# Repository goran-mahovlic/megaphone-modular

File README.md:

# megaphone-r5-modular
Modularised MEGAphone Design

This project is being carried out with the support of the NLnet Foundation under: https://nlnet.nl/project/MEGA65-MVP/

The goal of this project is to push the MEGAphone forward towards a Minimum Viable Product (MVP) in a cost-effective way by modularising the PCB
allowing for faster development and lower development costs as a result. Also, the modularisation helps to work around supply-chain problems by
allowing the replacement of hard to source components, without requiring a full PCB redesign.  Those modules can also be manufactured much more easily
in a domestic setting, as there is less cumulative chance of messing something up.  Alternatively, they can be manufactured in modest sized batches
using PCB fabrication places like PCBWay, who also offer an assembly option.

The following sections outline the tasks and their current state of progress, where appropriate.

## Task 1: Development and testing of core simple cellular telephony and text messaging software

The software aspect of this project relates to the software required to control and interact with the hardware modules, as well as to perform basic telephony functionality.

## Task 2: Modularisation and testing of the PCB design

The major hardware stream of this project is focused on modularising the MEGAphone PCB, so that the modules can be iterated and/or manufactured independently. This is to support both users self-manufacturing, so that the complexity of the fabrication process can be greatly simplified, as well as to allow for much faster and, including ad-hoc response to future supply chain challenges. 

### 2.1 High-efficiency DC-DC converter module to power the various sub-systems

High-current and high-efficiency modules are required for the main FPGA, cellular modem, auxilliary communications module, LCD panel, and external speaker/bluetooth modules.  It is desirable to come up with a single module that can be reused several times for these purposes.  The cellular modems are likely to be the highest draw item, and according to https://ww1.microchip.com/downloads/en/Appnotes/ANLPS300-APID.pdf, they can draw upto around 2A at 3.3V, which is the voltage we will most likely use, since it allows a common voltage for many of our sub-systems.

It is unlikely that any other device on the system will consume more power than this, so our DC-DC modules need to support 2A.

A further requirement is that it must be buck-boost, as the LiFePO4 cells can go below 3.3V, but when charged are >3.3V.

Some possible parts to consider:

STBBJ3 https://www.st.com/en/power-management/stbb3j.html  (2A in buck mode, i.e., where VIN > 3.3V, but only 800mA in boost mode, i.e., where VIN < 3.3V). 5x4 grid array, without thermal pad. Shutdown and soft-start. "typical" efficiency of 94%
LTC3113 https://www.analog.com/media/en/technical-documentation/data-sheets/3113f.pdf (3A in buck mode, 1.5A in boost mode). "up to" 96% efficiency. Choice of grid array and TSSOP -- but with a concealled thermal pad on the underside, which is not easy to hand-solder. AU$20 each for TTSOP!

### 2.2 Low-energy power-management module to minimise energy consumption of device, especially in low-power modes

### 2.3 Battery management and energy harvesting module to allow USB-C, integrated solar panel and external 12/24V vehicle battery power sources, and efficient management of the integrated rechargeable battery

### 2.4 Cellular modem communications module, including SIM card module

### 2.5 Internal microphone and speaker module

### 2.6 External speaker and bluetooth headset interface module

### 2.7 Primary FPGA carrier module, leveraging off-the-shelf FPGA modules if at all possible

### 2.8 LCD panel interface module

### 2.9 Auxiliary communications module, e.g., LoRa, ultra-sonic, infra-red or mm wave

Low-cost LoRa devices based on the SX1262 look to be an option, using open-source software like this: https://github.com/beegee-tokyo/SX126x-Mesh-Network
The goal would be for the module to be able to autonomously participate in the mesh while the main process is off.  ESP32s can go into low power modes with <1mA consumption according to https://www.arrow.com/en/research-and-events/articles/esp32-power-consumption-can-be-reduced-with-sleep-modes, and the SX1262 uses only about 5mA to listen for packets, and perhaps 70mA when active, so this looks plausible. The SX1262 when transmitting can draw upto about 120mA according to https://semtech.my.salesforce.com/sfc/p/#E0000000JelG/a/2R000000Un7F/yT.fKdAr9ZAo3cJLc4F2cBdUsMftpT2vsOICP7NmvMo

Thus the total power consumption of an auxilliary communications module (assuming we include an ESP32 in it, rather than using the power management FPGA to run the mesh) will be about 5mA while idle (~17mW) and upto ~200mA (~660mW).

### 2.10 Main carrier board and assembly, into which the various modules connect

## Task 3: Integration, Integration testing and remediation of the modules

Once the modules have been tested independently, this activity is focussed on testing the behaviour of the modules when connected to one another, including any VHDL/FPGA programming required to achieve this.

### 3.1 Requirements specification and analysis

### 3.2 Hardware integration and testing, including FPGA programming

### 3.3 Software integration and testing

### 3.4 Engage with and respond to security and accessibility audits

### 3.5 Remediation and contingency – for addressing any issues with the software and/or hardware components identified during the integration, and implementing or documenting appropriate solutions and/or work-arounds as appropriate

## Task 4: Preparation of Prototype Units

This activity focuses on taking the integrated hardware and software modules, and building a small number of units that are alpha-quality prototypes.  The specific objective is that they be integrated into units that are suitable for developers to use to continue development of both hardware and software of the system.  These units may be somewhat larger than the final obtainable footprint, depending on the costs of designing and fabricating the housings/enclosures.  The limited budget prevents the engagement of industrial designers who would be required for the completion of design for manufacture. Instead, we anticipate that the enclosures will be relatively simple 3D printed designs.
The remediation budget line is to allow for adjustment to the case design, the fabricated case and/or any of the hardware modules, so that the prototypes can be assembled and be as functional as possible.

### 4.1 Case Design

### 4.2 Case Fabrication

### 4.3 Assembly

### 4.4 Remediation / Mitigation, e.g., of any fitment issues, whether by adjustment of the case, reworking of a module or other means.

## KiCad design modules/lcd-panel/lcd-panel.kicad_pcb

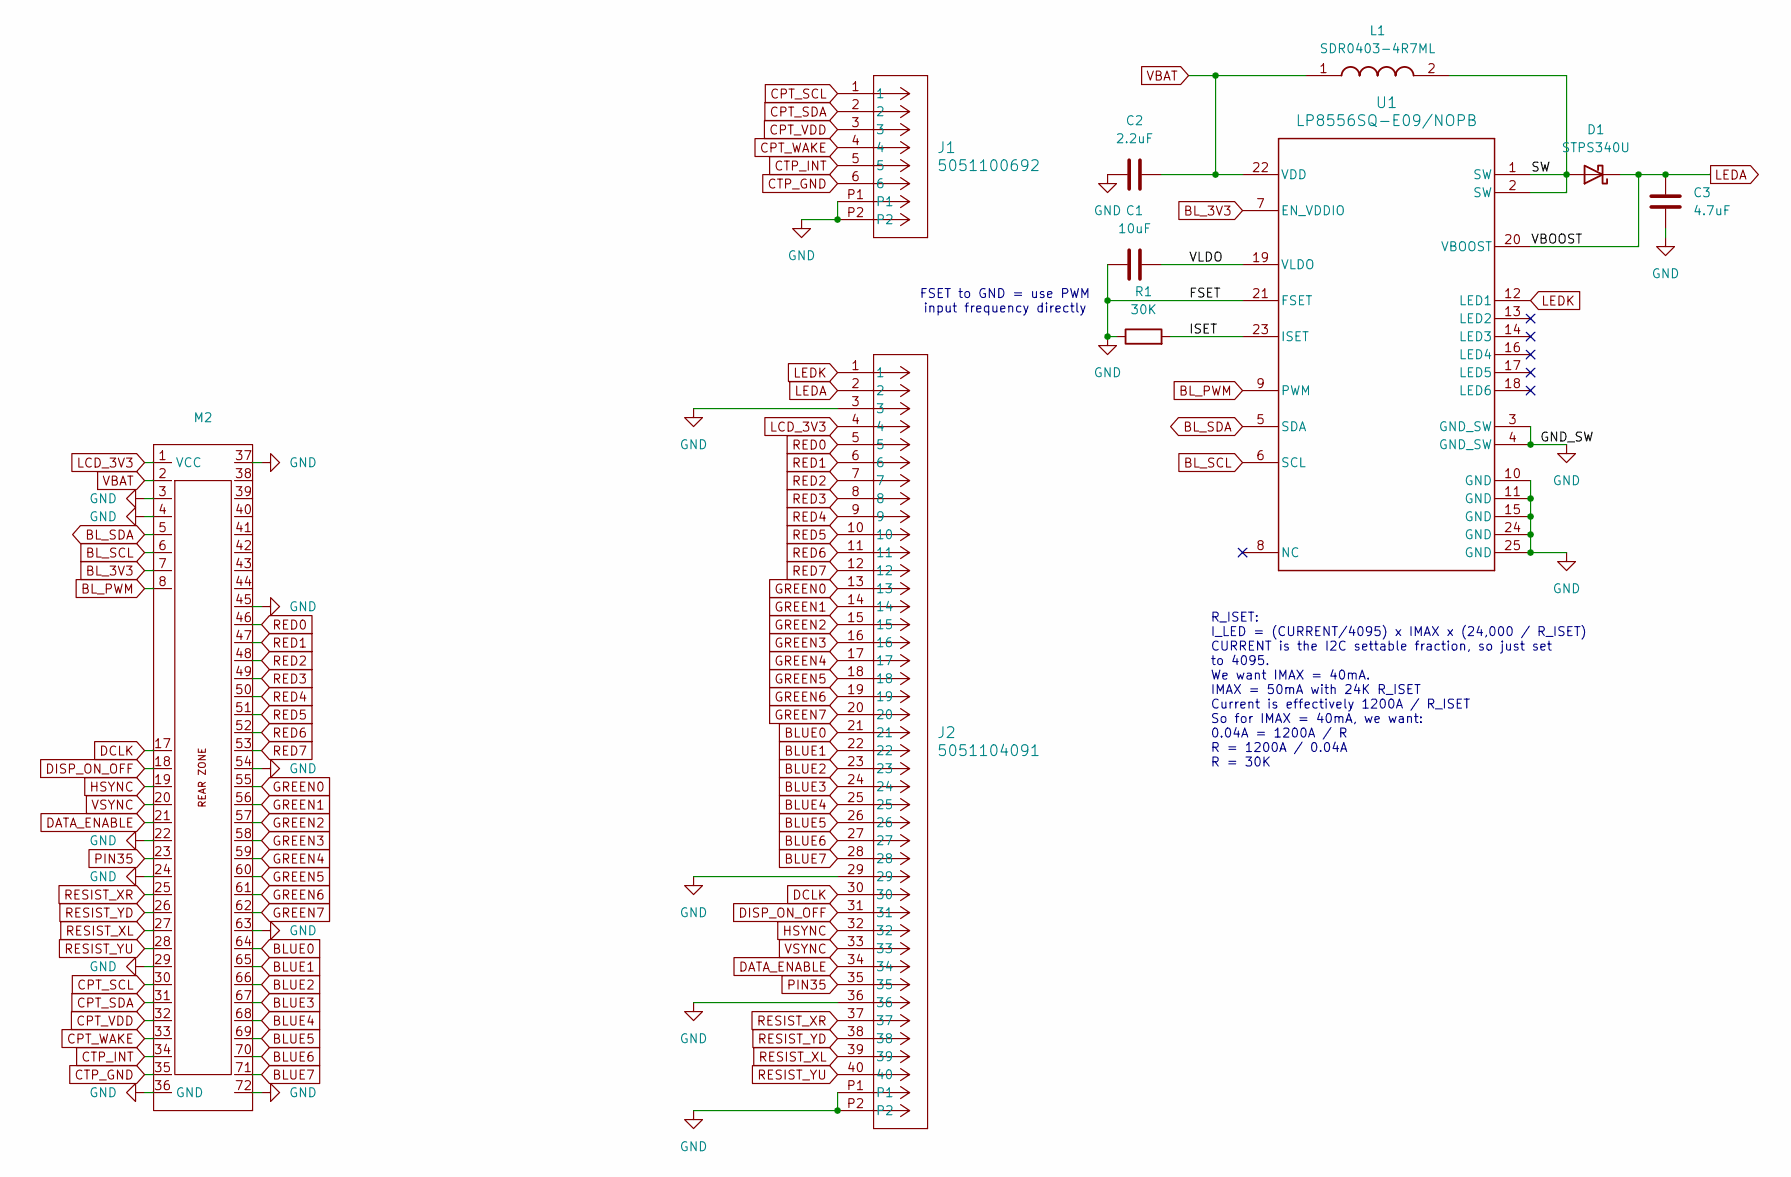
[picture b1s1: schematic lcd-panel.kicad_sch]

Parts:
C1: 10uF; C_0603_1608Metric_Pad1.08x0.95mm_HandSolder
C2: 2.2uF; C_0603_1608Metric_Pad1.08x0.95mm_HandSolder
C3: 4.7uF; C_0603_1608Metric_Pad1.08x0.95mm_HandSolder
D1: STPS340U; D_SOD-123
J1: 5051100692; CON_5051100692_MOL
J2: 5051104091; CON_5051104091_MOL
L1: SDR0403-4R7ML; SDR0403; Mouser Part Number 652-SDR0403-4R7ML
M2: MegaCastle2x36-Module-I40.0x86.6-MFFFFFFFFFFFFFF-SPAREPAD
R1: 30K; R_0603_1608Metric_Pad0.98x0.95mm_HandSolder
U1: LP8556SQ-E09/NOPB; RTW0024A

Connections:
/ISET: R1.2, U1.23 (ISET)
/SW: D1.2 (A), L1.2, U1.1 (SW), U1.2 (SW)
/VLDO: C1.2, U1.19 (VLDO)
BLUE0: J2.21, M2.64
BLUE1: J2.22, M2.65
BLUE2: J2.23, M2.66
BLUE3: J2.24, M2.67
BLUE4: J2.25, M2.68
BLUE5: J2.26, M2.69
BLUE6: J2.27, M2.70
BLUE7: J2.28, M2.71
BL_3V3: M2.7, U1.7 (EN_VDDIO)
BL_PWM: M2.8, U1.9 (PWM)
BL_SCL: M2.6, U1.6 (SCL)
BL_SDA: M2.5, U1.5 (SDA)
CPT_SCL: J1.1, M2.30
CPT_SDA: J1.2, M2.31
CPT_VDD: J1.3, M2.32
CPT_WAKE: J1.4, M2.33
CTP_GND: J1.6, M2.35
CTP_INT: J1.5, M2.34
DATA_ENABLE: J2.34, M2.21
DCLK: J2.30, M2.17
DISP_ON_OFF: J2.31, M2.18
GND: C1.1, C2.1, C3.2, J1.P1, J1.P2, J2.3, J2.29, J2.36, J2.P1, J2.P2, M2.3, M2.4, M2.22, M2.24, M2.29, M2.36 (GND), M2.37, M2.45, M2.54, M2.63, M2.72, R1.1, U1.3 (GND_SW), U1.4 (GND_SW), U1.10 (GND), U1.11 (GND), U1.15 (GND), U1.21 (FSET), U1.24 (GND), U1.25 (GND)
GREEN0: J2.13, M2.55
GREEN1: J2.14, M2.56
GREEN2: J2.15, M2.57
GREEN3: J2.16, M2.58
GREEN4: J2.17, M2.59
GREEN5: J2.18, M2.60
GREEN6: J2.19, M2.61
GREEN7: J2.20, M2.62
HSYNC: J2.32, M2.19
LCD_3V3: J2.4, M2.1 (VCC)
LEDA: C3.1, D1.1 (K), J2.2, U1.20 (VBOOST)
LEDK: J2.1, U1.12 (LED1)
PIN35: J2.35, M2.23
RED0: J2.5, M2.46
RED1: J2.6, M2.47
RED2: J2.7, M2.48
RED3: J2.8, M2.49
RED4: J2.9, M2.50
RED5: J2.10, M2.51
RED6: J2.11, M2.52
RED7: J2.12, M2.53
RESIST_XL: J2.39, M2.27
RESIST_XR: J2.37, M2.25
RESIST_YD: J2.38, M2.26
RESIST_YU: J2.40, M2.28
VBAT: C2.2, L1.1, M2.2, U1.22 (VDD)
VSYNC: J2.33, M2.20

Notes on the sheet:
FSET to GND = use PWM input frequency directly
R_ISET: I_LED = (CURRENT/4095) x IMAX x (24,000 / R_ISET) CURRENT is the I2C settable fraction, so just set to 4095. We want IMAX = 40mA. IMAX = 50mA with 24K R_ISET Current is effectively 1200A / R_ISET So for IMAX = 40mA, we want: 0.04A = 1200A / R R = 1200A / 0.04A R = 30K

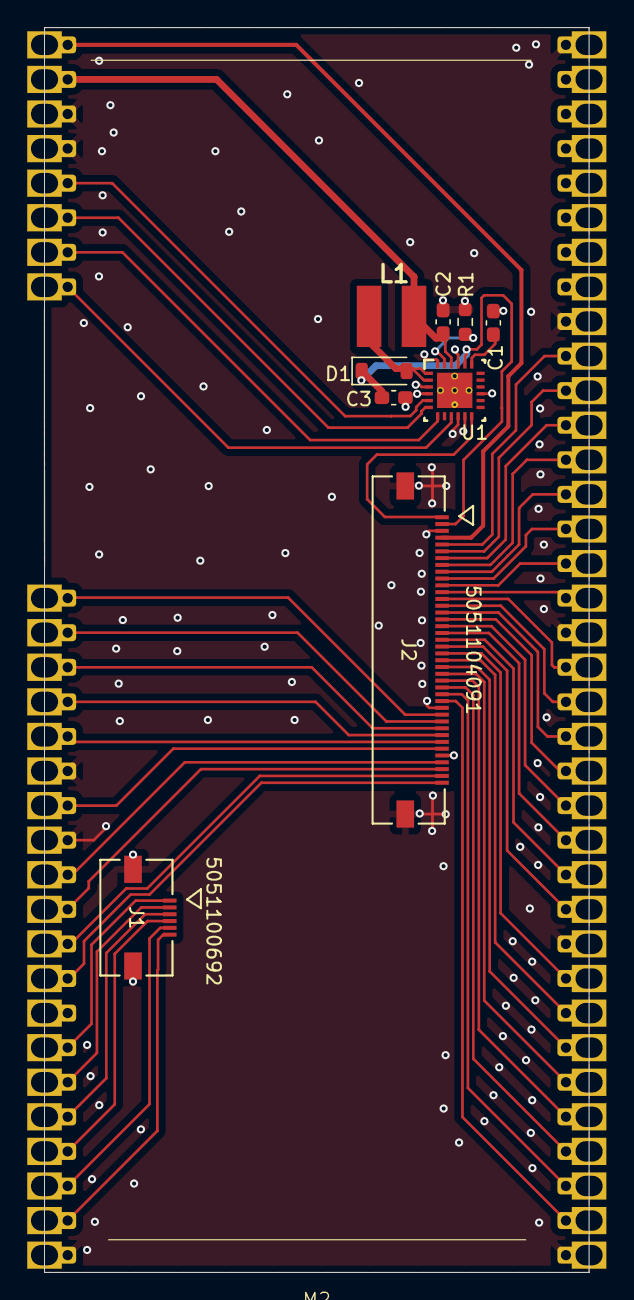
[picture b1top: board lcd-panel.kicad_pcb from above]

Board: 4 copper layers, 40.0 x 91.4 mm, 10 parts (0 on the bottom side), 52 nets.

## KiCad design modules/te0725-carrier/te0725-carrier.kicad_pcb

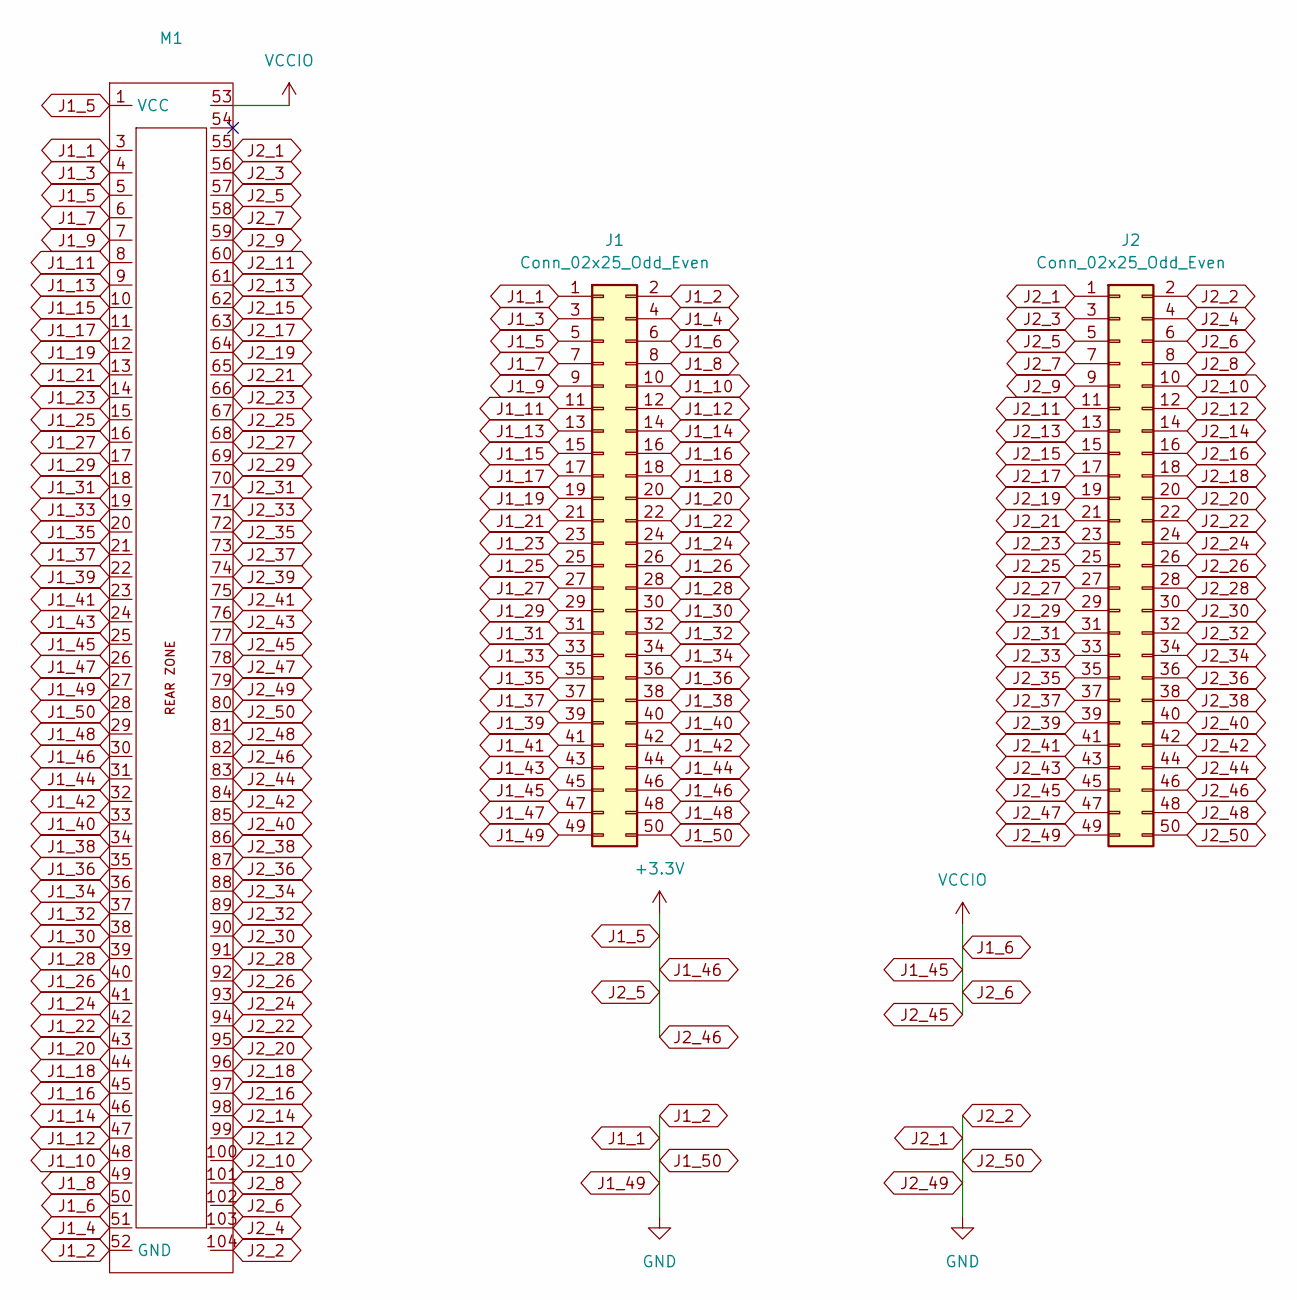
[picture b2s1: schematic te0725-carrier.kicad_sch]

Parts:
J1, J2: Conn_02x25_Odd_Even; PinHeader_2x25_P2.54mm_Vertical
M1: MegaCastle2x52-Module-I42.0x127.3-M1

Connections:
J1_1: J1.1, J1.2, J1.49, J1.50, J2.1, J2.2, J2.49, J2.50, M1.3, M1.27, M1.28, M1.52 (GND), M1.55, M1.79, M1.80, M1.104
J1_3: J1.3, M1.4
J1_4: J1.4, M1.51
J1_7: J1.7, M1.6
J1_8: J1.8, M1.49
J1_9: J1.9, M1.7
J1_10: J1.10, M1.48
J1_11: J1.11, M1.8
J1_12: J1.12, M1.47
J1_13: J1.13, M1.9
J1_14: J1.14, M1.46
J1_15: J1.15, M1.10
J1_16: J1.16, M1.45
J1_17: J1.17, M1.11
J1_18: J1.18, M1.44
J1_19: J1.19, M1.12
J1_20: J1.20, M1.43
J1_21: J1.21, M1.13
J1_22: J1.22, M1.42
J1_23: J1.23, M1.14
J1_24: J1.24, M1.41
J1_25: J1.25, M1.15
J1_26: J1.26, M1.40
J1_27: J1.27, M1.16
J1_28: J1.28, M1.39
J1_29: J1.29, M1.17
J1_30: J1.30, M1.38
J1_31: J1.31, M1.18
J1_32: J1.32, M1.37
J1_33: J1.33, M1.19
J1_34: J1.34, M1.36
J1_35: J1.35, M1.20
J1_36: J1.36, M1.35
J1_37: J1.37, M1.21
J1_38: J1.38, M1.34
J1_39: J1.39, M1.22
J1_40: J1.40, M1.33
J1_41: J1.41, M1.23
J1_42: J1.42, M1.32
J1_43: J1.43, M1.24
J1_44: J1.44, M1.31
J1_45: J1.6, J1.45, J2.6, J2.45, M1.25, M1.50, M1.53, M1.77, M1.102
J1_46: J1.5, J1.46, J2.5, J2.46, M1.1 (VCC), M1.5, M1.30, M1.57, M1.82
J1_47: J1.47, M1.26
J1_48: J1.48, M1.29
J2_3: J2.3, M1.56
J2_4: J2.4, M1.103
J2_7: J2.7, M1.58
J2_8: J2.8, M1.101
J2_9: J2.9, M1.59
J2_10: J2.10, M1.100
J2_11: J2.11, M1.60
J2_12: J2.12, M1.99
J2_13: J2.13, M1.61
J2_14: J2.14, M1.98
J2_15: J2.15, M1.62
J2_16: J2.16, M1.97
J2_17: J2.17, M1.63
J2_18: J2.18, M1.96
J2_19: J2.19, M1.64
J2_20: J2.20, M1.95
J2_21: J2.21, M1.65
J2_22: J2.22, M1.94
J2_23: J2.23, M1.66
J2_24: J2.24, M1.93
J2_25: J2.25, M1.67
J2_26: J2.26, M1.92
J2_27: J2.27, M1.68
J2_28: J2.28, M1.91
J2_29: J2.29, M1.69
J2_30: J2.30, M1.90
J2_31: J2.31, M1.70
J2_32: J2.32, M1.89
J2_33: J2.33, M1.71
J2_34: J2.34, M1.88
J2_35: J2.35, M1.72
J2_36: J2.36, M1.87
J2_37: J2.37, M1.73
J2_38: J2.38, M1.86
J2_39: J2.39, M1.74
J2_40: J2.40, M1.85
J2_41: J2.41, M1.75
J2_42: J2.42, M1.84
J2_43: J2.43, M1.76
J2_44: J2.44, M1.83
J2_47: J2.47, M1.78
J2_48: J2.48, M1.81

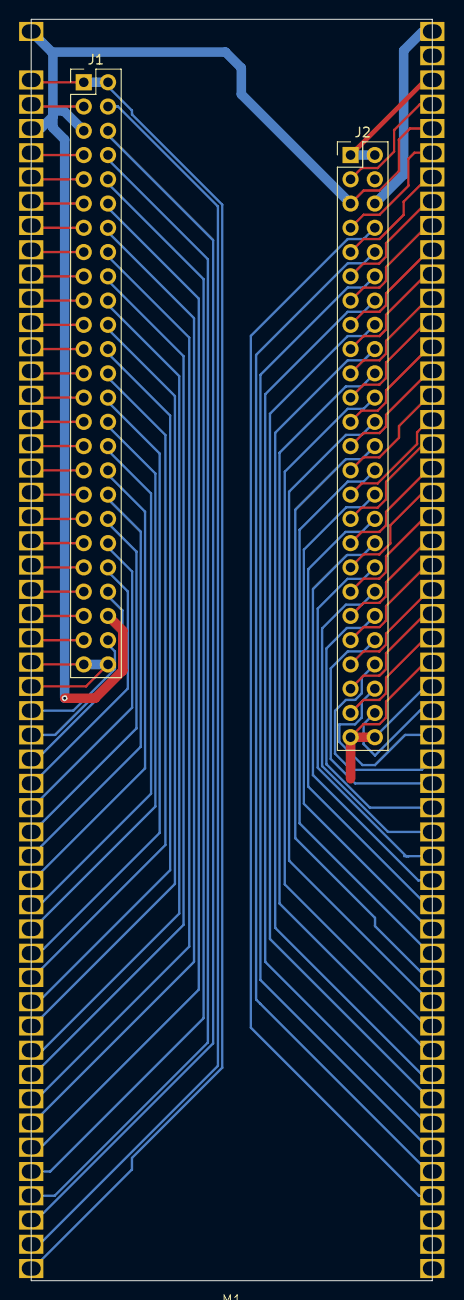
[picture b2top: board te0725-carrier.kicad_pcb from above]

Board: 2 copper layers, 42.0 x 132.1 mm, 3 parts (0 on the bottom side), 87 nets.

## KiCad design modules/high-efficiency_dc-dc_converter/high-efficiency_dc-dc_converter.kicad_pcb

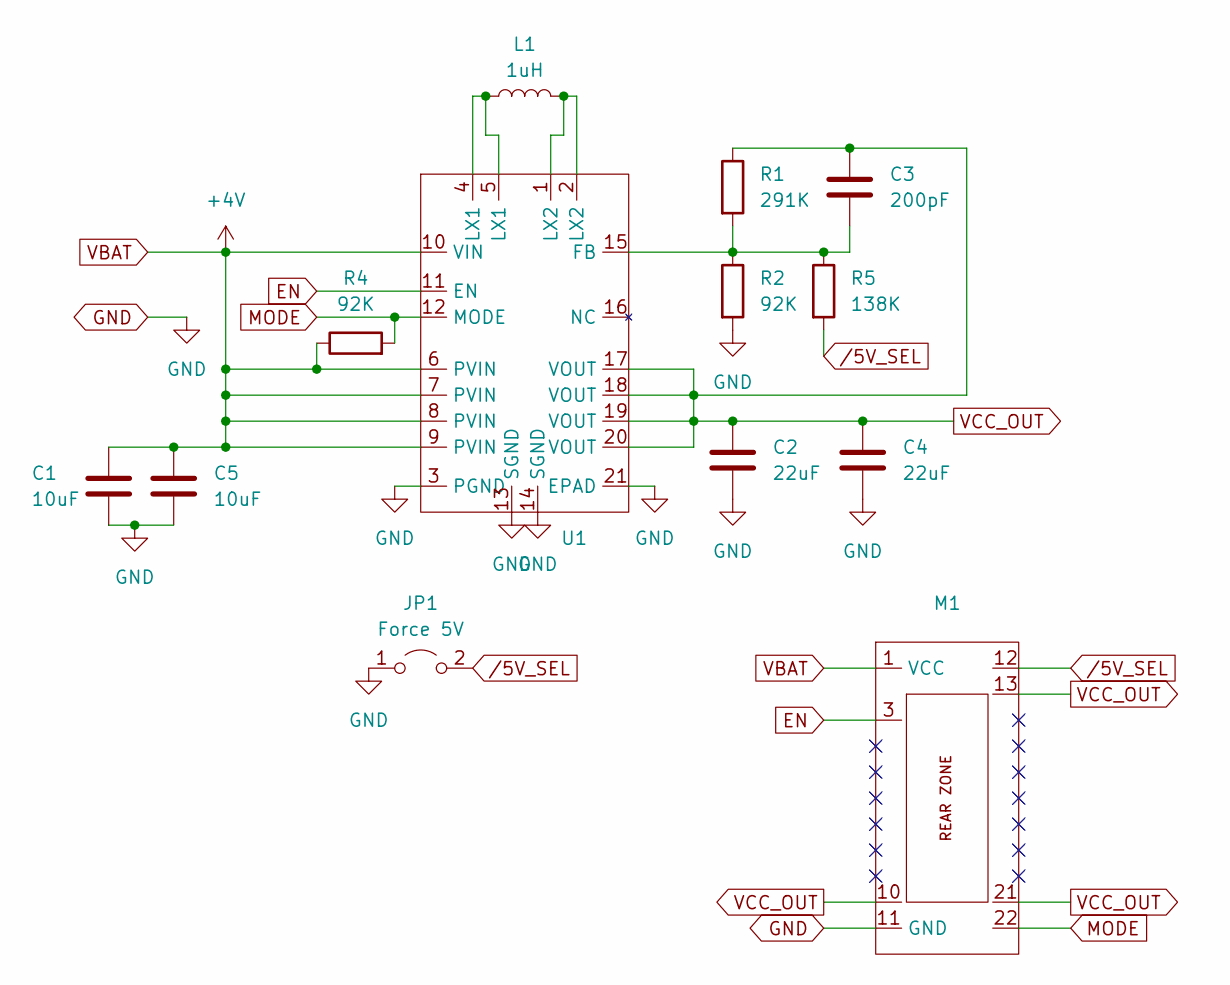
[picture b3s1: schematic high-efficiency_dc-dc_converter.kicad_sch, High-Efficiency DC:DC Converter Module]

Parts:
C1, C5: 10uF; C_0805_2012Metric
C2, C4: 22uF; C_0805_2012Metric
C3: 200pF; C_0805_2012Metric
JP1: Force 5V; SolderJumper-2_P1.3mm_Open_RoundedPad1.0x1.5mm
L1: 1uH; L_1008_2520Metric
M1: MegaCastle2x11-Module-I15.7x23.1-MA0780C-PANEL-NIBBLE
R1: 291K; R_0603_1608Metric
R2, R4: 92K; R_0603_1608Metric
R5: 138K; R_0603_1608Metric
U1: QFN50P400X400X90-21N

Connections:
EN: M1.3, U1.11 (EN)
GND: C1.2, C2.2, C4.2, C5.2, JP1.1 (A), M1.11 (GND), R2.2, U1.3 (PGND), U1.13 (SGND), U1.14 (SGND), U1.21 (EPAD)
MODE: M1.22, R4.2, U1.12 (MODE)
unnamed: L1.1, U1.4 (LX1), U1.5 (LX1)
unnamed: L1.2, U1.1 (LX2), U1.2 (LX2)
unnamed: C3.2, R1.2, R2.1, R5.1, U1.15 (FB)
VBAT: C1.1, C5.1, M1.1 (VCC), R4.1, U1.6 (PVIN), U1.7 (PVIN), U1.8 (PVIN), U1.9 (PVIN), U1.10 (VIN)
VCC_OUT: C2.1, C3.1, C4.1, M1.10, M1.13, M1.21, R1.1, U1.17 (VOUT), U1.18 (VOUT), U1.19 (VOUT), U1.20 (VOUT)
/5V_SEL: JP1.2 (B), M1.12, R5.2

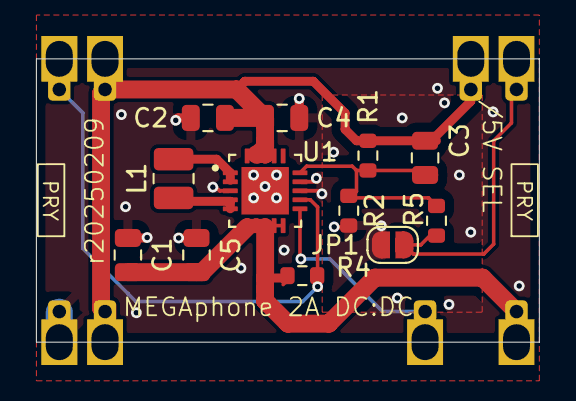
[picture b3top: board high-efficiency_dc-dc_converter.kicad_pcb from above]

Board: 2 copper layers, 27.9 x 15.7 mm, 13 parts (1 on the bottom side), 9 nets.

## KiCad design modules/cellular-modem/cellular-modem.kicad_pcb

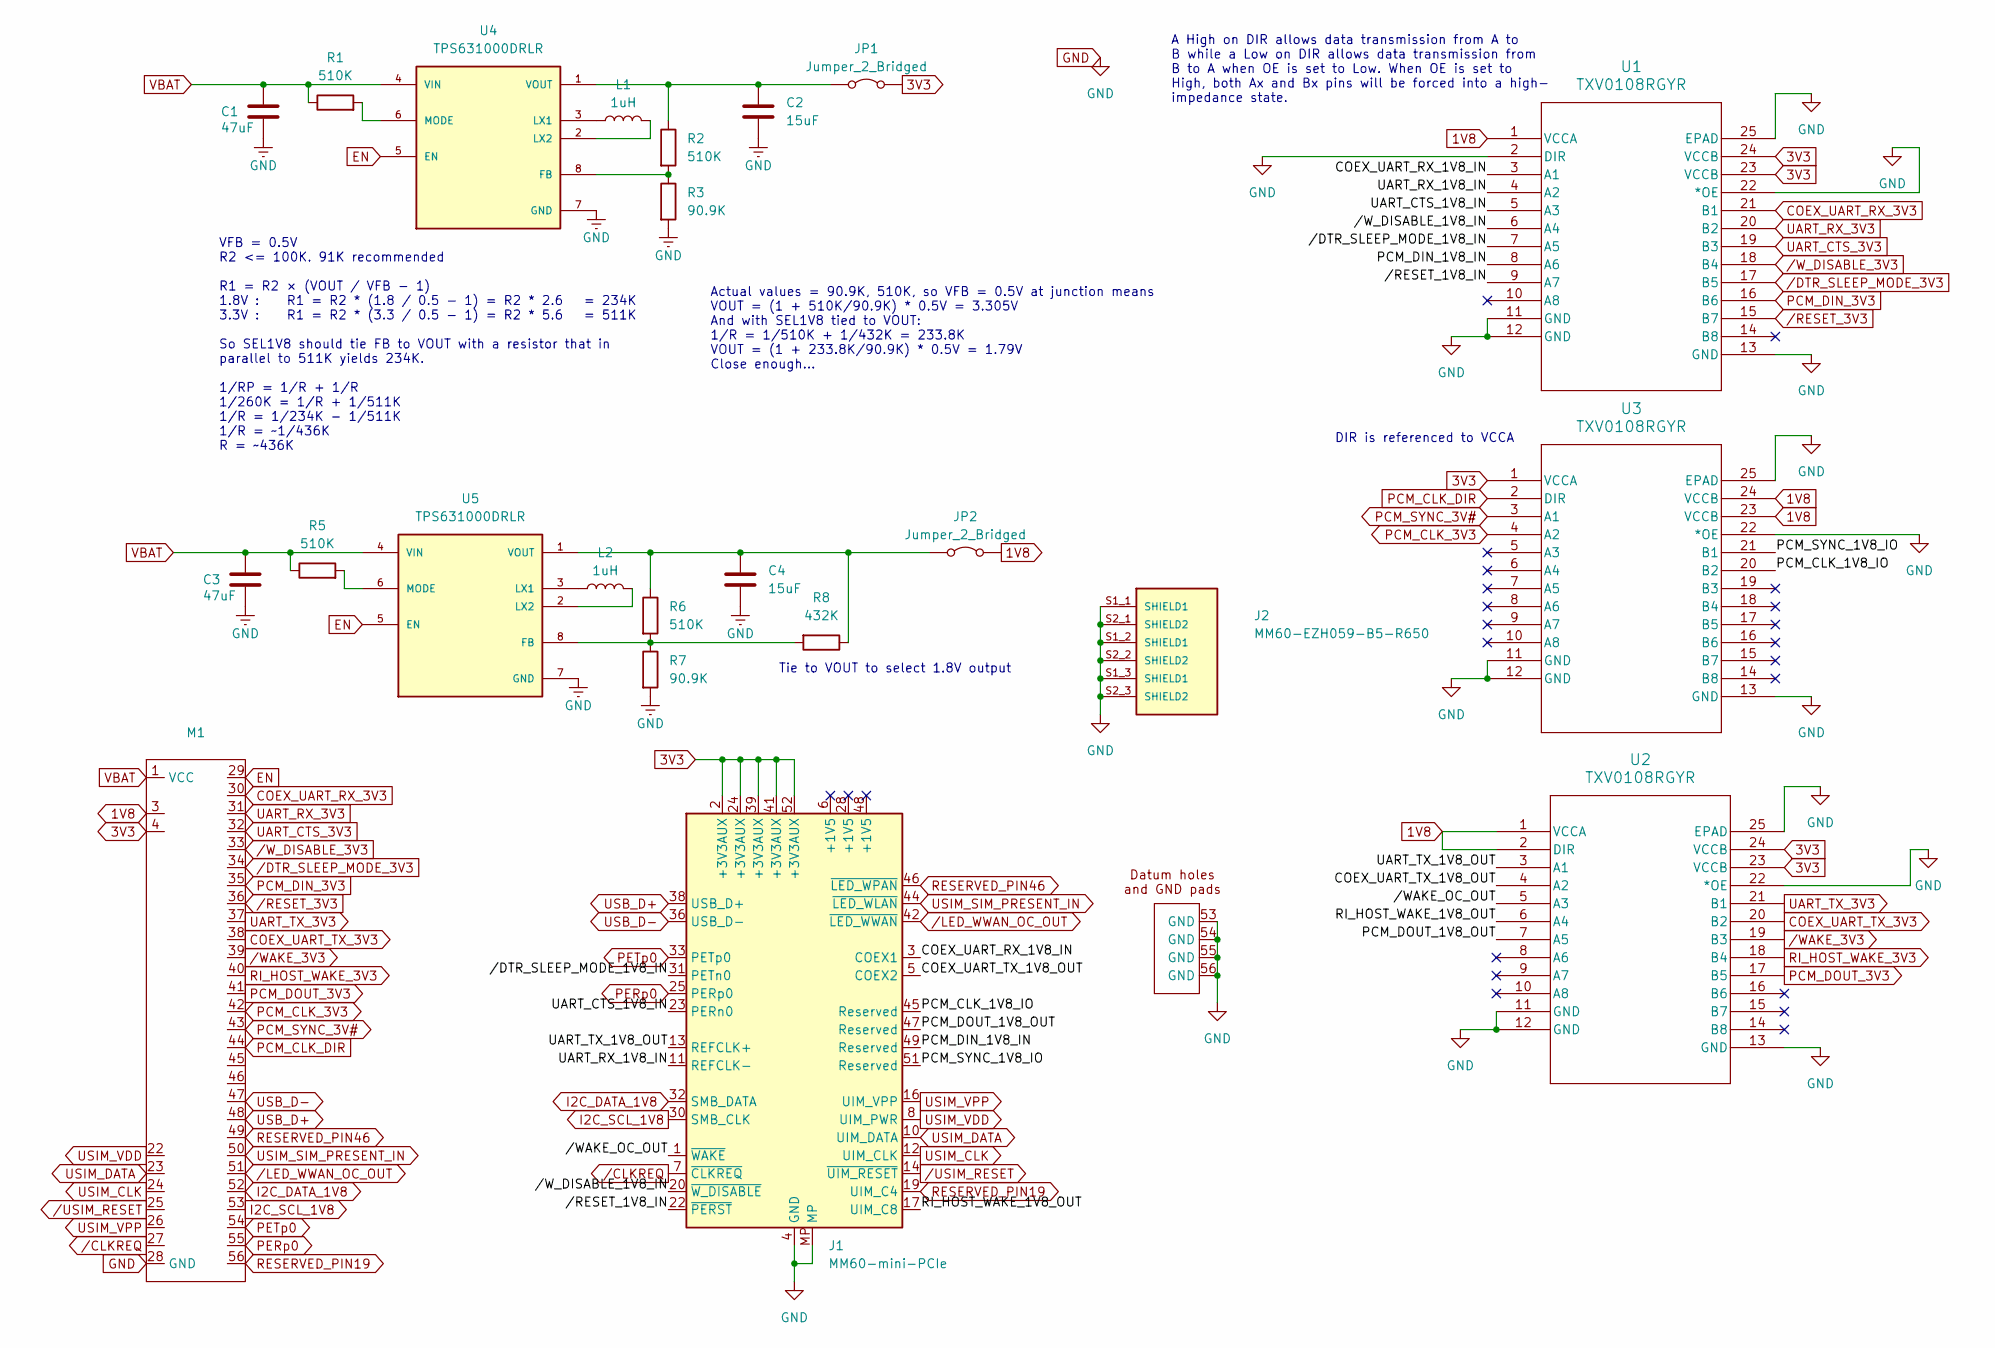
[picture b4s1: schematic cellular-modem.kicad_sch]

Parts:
C1, C3: 47uF; C_0805_2012Metric
C2, C4: 15uF; C_0805_2012Metric
J1: MM60-mini-PCIe; CONN_MM60-52B1-E1-R650_JAE
J2: MM60-EZH059-B5-R650; JAE_MM60-EZH059-B5-R650; PARTREV 3
JP1, JP2: Jumper_2_Bridged; SolderJumper-2_P1.3mm_Bridged2Bar_RoundedPad1.0x1.5mm
L1, L2: 1uH; L_1008_2520Metric_Pad1.43x2.20mm_HandSolder
M1: MegaCastle2x28-Module-I36.0x66.3-MB00007FFFFFFFF-NIBBLE
R1, R2, R5, R6: 510K; R_0805_2012Metric
R3, R7: 90.9K; R_0805_2012Metric
R8: 432K; R_0805_2012Metric
U1, U2, U3: TXV0108RGYR; VQFN24_RGY_TEX
U4, U5: TPS631000DRLR; SOT50P160X60-8N; PARTREV B

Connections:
1V8: JP2.2 (B), M1.3, U1.1 (VCCA), U2.1 (VCCA), U2.2 (DIR), U3.23 (VCCB), U3.24 (VCCB)
3V3: J1.2 (+3V3AUX), J1.24 (+3V3AUX), J1.39 (+3V3AUX), J1.41 (+3V3AUX), J1.52 (+3V3AUX), JP1.2 (B), M1.4, U1.23 (VCCB), U1.24 (VCCB), U2.23 (VCCB), U2.24 (VCCB), U3.1 (VCCA)
/COEX_UART_RX_1V8_IN: J1.3 (COEX1), U1.3 (A1)
/COEX_UART_TX_1V8_OUT: J1.5 (COEX2), U2.4 (A2)
/PCM_CLK_1V8_IO: J1.45 (Reserved), U3.20 (B2)
/PCM_DIN_1V8_IN: J1.49 (Reserved), U1.8 (A6)
/PCM_DOUT_1V8_OUT: J1.47 (Reserved), U2.7 (A5)
/PCM_SYNC_1V8_IO: J1.51 (Reserved), U3.21 (B1)
/RI_HOST_WAKE_1V8_OUT: J1.17 (UIM_C8), U2.6 (A4)
/UART_CTS_1V8_IN: J1.23 (PERn0), U1.5 (A3)
/UART_RX_1V8_IN: J1.11 (REFCLK-), U1.4 (A2)
/UART_TX_1V8_OUT: J1.13 (REFCLK+), U2.3 (A1)
//DTR_SLEEP_MODE_1V8_IN: J1.31 (PETn0), U1.7 (A5)
//RESET_1V8_IN: J1.22 (~PERST), U1.9 (A7)
//WAKE_OC_OUT: J1.1 (~WAKE), U2.5 (A3)
//W_DISABLE_1V8_IN: J1.20 (~W_DISABLE), U1.6 (A4)
COEX_UART_RX_3V3: M1.30, U1.21 (B1)
COEX_UART_TX_3V3: M1.38, U2.20 (B2)
EN: M1.29, U4.5 (EN), U5.5 (EN)
GND: C1.1, C2.2, C3.1, C4.2, J1.4 (GND), J1.9 (GND), J1.15 (GND), J1.18 (GND), J1.21 (GND), J1.26 (GND), J1.27 (GND), J1.29 (GND), J1.34 (GND), J1.35 (GND), J1.37 (GND), J1.40 (GND), J1.43 (GND), J1.50 (GND), J1.53 (GND), J1.54 (GND), J1.55 (GND), J1.56 (GND), J1.MP, J2.S1_1 (SHIELD1), J2.S1_2 (SHIELD1), J2.S1_3 (SHIELD1), J2.S2_1 (SHIELD2), J2.S2_2 (SHIELD2), J2.S2_3 (SHIELD2), M1.28 (GND), R3.2, R7.2, U1.2 (DIR), U1.11 (GND), U1.12 (GND), U1.13 (GND), U1.22 (*OE), U1.25 (EPAD), U2.11 (GND), U2.12 (GND), U2.13 (GND), U2.22 (*OE), U2.25 (EPAD), U3.11 (GND), U3.12 (GND), U3.13 (GND), U3.22 (*OE), U3.25 (EPAD), U4.7 (GND), U5.7 (GND)
I2C_DATA_1V8: J1.32 (SMB_DATA), M1.52
I2C_SCL_1V8: J1.30 (SMB_CLK), M1.53
unnamed: C2.1, JP1.1 (A), R2.1, U4.1 (VOUT)
unnamed: C4.1, JP2.1 (A), R6.1, R8.1, U5.1 (VOUT)
unnamed: R2.2, R3.1, U4.8 (FB)
unnamed: L1.1, U4.3 (LX1)
unnamed: L1.2, U4.2 (LX2)
unnamed: R1.2, U4.6 (MODE)
unnamed: R6.2, R7.1, R8.2, U5.8 (FB)
unnamed: L2.1, U5.3 (LX1)
unnamed: L2.2, U5.2 (LX2)
unnamed: R5.2, U5.6 (MODE)
PCM_CLK_3V3: M1.42, U3.4 (A2)
PCM_CLK_DIR: M1.44, U3.2 (DIR)
PCM_DIN_3V3: M1.35, U1.16 (B6)
PCM_DOUT_3V3: M1.41, U2.17 (B5)
PCM_SYNC_3V#: M1.43, U3.3 (A1)
PERp0: J1.25 (PERp0), M1.55
PETp0: J1.33 (PETp0), M1.54
RESERVED_PIN19: J1.19 (UIM_C4), M1.56
RESERVED_PIN46: J1.46 (~LED_WPAN), M1.49
RI_HOST_WAKE_3V3: M1.40, U2.18 (B4)
UART_CTS_3V3: M1.32, U1.19 (B3)
UART_RX_3V3: M1.31, U1.20 (B2)
UART_TX_3V3: M1.37, U2.21 (B1)
USB_D+: J1.38 (USB_D+), M1.48
USB_D-: J1.36 (USB_D-), M1.47
USIM_CLK: J1.12 (UIM_CLK), M1.24
USIM_DATA: J1.10 (UIM_DATA), M1.23
USIM_SIM_PRESENT_IN: J1.44 (~LED_WLAN), M1.50
USIM_VDD: J1.8 (UIM_PWR), M1.22
USIM_VPP: J1.16 (UIM_VPP), M1.26
VBAT: C1.2, C3.2, M1.1 (VCC), R1.1, R5.1, U4.4 (VIN), U5.4 (VIN)
/CLKREQ: J1.7 (~CLKREQ), M1.27
/DTR_SLEEP_MODE_3V3: M1.34, U1.17 (B5)
/LED_WWAN_OC_OUT: J1.42 (~LED_WWAN), M1.51
/RESET_3V3: M1.36, U1.15 (B7)
/USIM_RESET: J1.14 (~UIM_RESET), M1.25
/WAKE_3V3: M1.39, U2.19 (B3)
/W_DISABLE_3V3: M1.33, U1.18 (B4)

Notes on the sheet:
Tie to VOUT to select 1.8V output
Actual values = 90.9K, 510K, so VFB = 0.5V at junction means VOUT = (1 + 510K/90.9K) * 0.5V = 3.305V And with SEL1V8 tied to VOUT: 1/R = 1/510K + 1/432K = 233.8K VOUT = (1 + 233.8K/90.9K) * 0.5V = 1.79V Close enough...
VFB = 0.5V R2 <= 100K. 91K recommended R1 = R2 × (VOUT / VFB - 1) 1.8V : R1 = R2 * (1.8 / 0.5 - 1) = R2 * 2.6 = 234K 3.3V : R1 = R2 * (3.3 / 0.5 - 1) = R2 * 5.6 = 511K So SEL1V8 should tie FB to VOUT with a resistor that in parallel to 511K yields 234K. 1/RP = 1/R + 1/R 1/260K = 1/R + 1/511K 1/R = 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
DIR is referenced to VCCA
A High on DIR allows data transmission from A to B while a Low on DIR allows data transmission from B to A when OE is set to Low. When OE is set to High, both Ax and Bx pins will be forced into a high- impedance state.

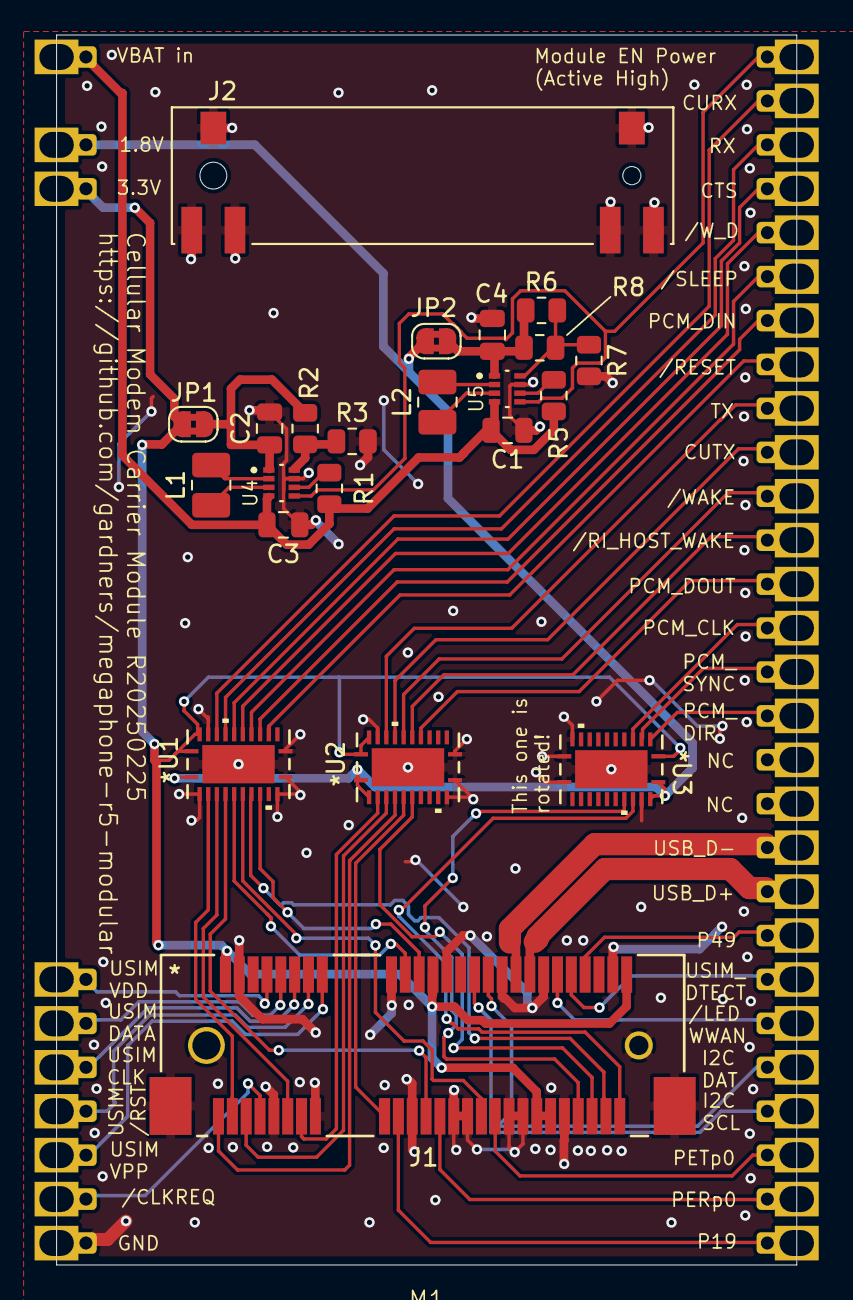
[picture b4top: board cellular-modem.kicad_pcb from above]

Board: 4 copper layers, 42.8 x 71.1 mm, 23 parts (0 on the bottom side), 60 nets.

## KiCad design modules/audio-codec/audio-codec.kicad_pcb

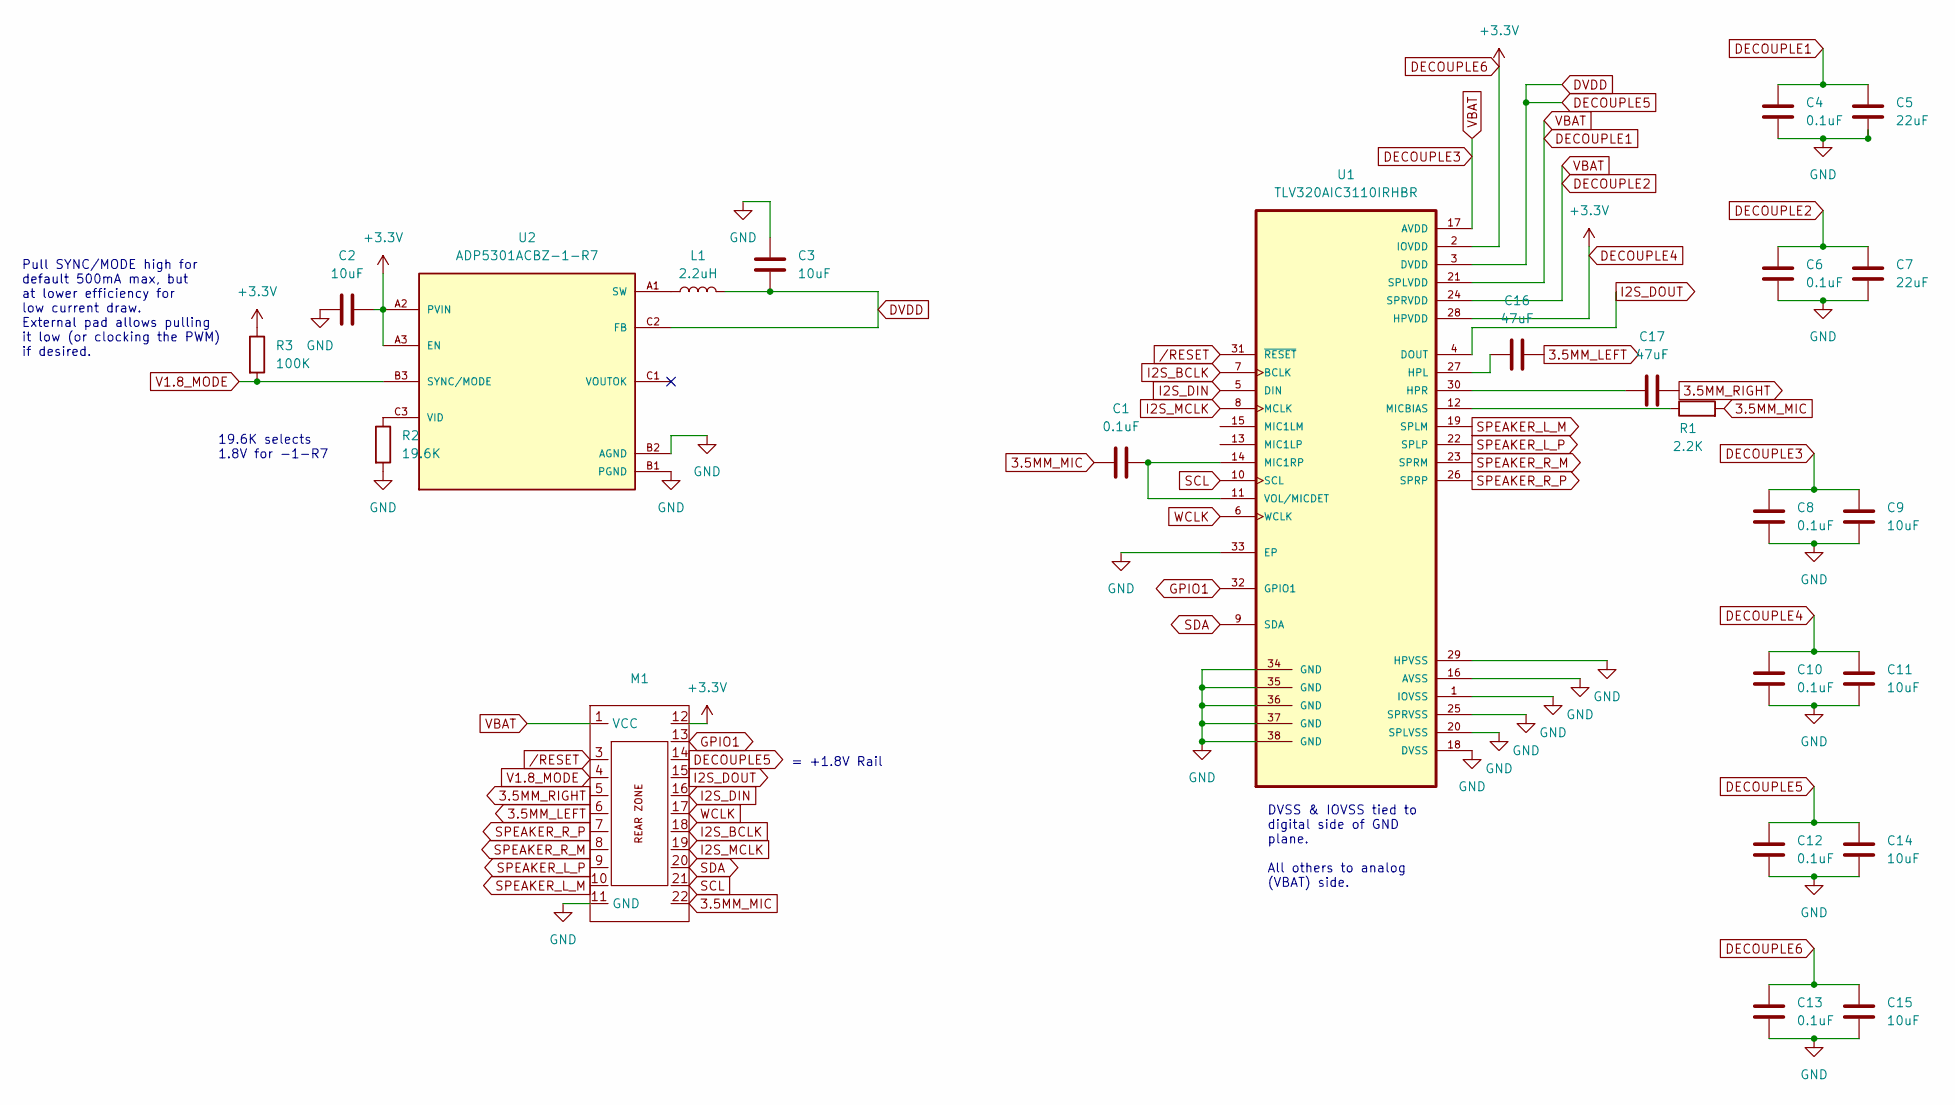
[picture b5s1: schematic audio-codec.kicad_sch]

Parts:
C1, C4, C6, C8, C10, C12, C13: 0.1uF; C_0603_1608Metric; Mfr. PN C0603C104M4RAC; Mouser PN 80-C0603C104M4RAC
C2, C3, C9, C11, C14, C15: 10uF; C_0603_1608Metric; Mfr. PN C0603C106M9PAC7411; Mouser PN 80-C0603C106M9P7411
C5, C7: 22uF; C_0603_1608Metric; Mfr. PN CC0603MRX5R5BB226; Mouser PN 603-CC603MRX5R5BB226
C16, C17: 47uF; C_0603_1608Metric; Mfr. PN GRM188R60E476ME15J; Mouser PN 81-GRM188R60E476ME5J
L1: 2.2uH; L_0805_2012Metric; Mouser PN 810-MLP2016V2R2MT0S1
M1: MegaCastle2x11-Module-I22.0x23.1-MBFFFFC-SPAREPAD
R1: 2.2K; R_0603_1608Metric; Mfr. PN RT0603DRE072K2L; Mouser PN 603-RT0603DRE072K2L
R2: 19.6K; R_0603_1608Metric; Mouser PN 603-RT0603BRD0719K6L
R3: 100K; R_0603_1608Metric; Mouser PN 603-RC0603FR-07100KL
U1: TLV320AIC3110IRHBR; IC_ADS125H01IRHBT; Mouser PN 595-V320AIC3110IRHBR
U2: ADP5301ACBZ-1-R7; BGA9C50P3X3_187X165X66N; Mouser PN 584-ADP5301ACBZ-1-R7

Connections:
3.5MM_LEFT: C16.2, M1.6
3.5MM_MIC: C1.2, M1.22, R1.2
3.5MM_RIGHT: C17.2, M1.5
DECOUPLE1: C4.1, C5.1, C6.1, C7.1, C8.1, C9.1, M1.1 (VCC), U1.17 (AVDD), U1.21 (SPLVDD), U1.24 (SPRVDD)
DECOUPLE4: C2.2, C10.1, C11.1, C13.1, C15.1, M1.12, R3.1, U1.2 (IOVDD), U1.28 (HPVDD), U2.A2 (PVIN), U2.A3 (EN)
DECOUPLE5: C3.1, C12.1, C14.1, L1.2, M1.14, U1.3 (DVDD), U2.C2 (FB)
GND: C2.1, C3.2, C4.2, C5.2, C6.2, C7.2, C8.2, C9.2, C10.2, C11.2, C12.2, C13.2, C14.2, C15.2, M1.11 (GND), R2.2, U1.1 (IOVSS), U1.16 (AVSS), U1.18 (DVSS), U1.20 (SPLVSS), U1.25 (SPRVSS), U1.29 (HPVSS), U1.33 (EP), U1.34 (GND), U1.35 (GND), U1.36 (GND), U1.37 (GND), U1.38 (GND), U2.B1 (PGND), U2.B2 (AGND)
GPIO1: M1.13, U1.32 (GPIO1)
I2S_BCLK: M1.18, U1.7 (BCLK)
I2S_DIN: M1.16, U1.5 (DIN)
I2S_DOUT: M1.15, U1.4 (DOUT)
I2S_MCLK: M1.19, U1.8 (MCLK)
unnamed: C16.1, U1.27 (HPL)
unnamed: C17.1, U1.30 (HPR)
unnamed: C1.1, U1.11 (VOL/MICDET), U1.14 (MIC1RP)
unnamed: R1.1, U1.12 (MICBIAS)
unnamed: L1.1, U2.A1 (SW)
unnamed: R2.1, U2.C3 (VID)
SCL: M1.21, U1.10 (SCL)
SDA: M1.20, U1.9 (SDA)
SPEAKER_L_M: M1.10, U1.19 (SPLM)
SPEAKER_L_P: M1.9, U1.22 (SPLP)
SPEAKER_R_M: M1.8, U1.23 (SPRM)
SPEAKER_R_P: M1.7, U1.26 (SPRP)
V1.8_MODE: M1.4, R3.2, U2.B3 (SYNC/MODE)
WCLK: M1.17, U1.6 (WCLK)
/RESET: M1.3, U1.31 (~RESET)

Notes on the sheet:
Pull SYNC/MODE high for default 500mA max, but at lower efficiency for low current draw. External pad allows pulling it low (or clocking the PWM) if desired.
19.6K selects 1.8V for -1-R7
= +1.8V Rail
DVSS & IOVSS tied to digital side of GND plane. All others to analog (VBAT) side.

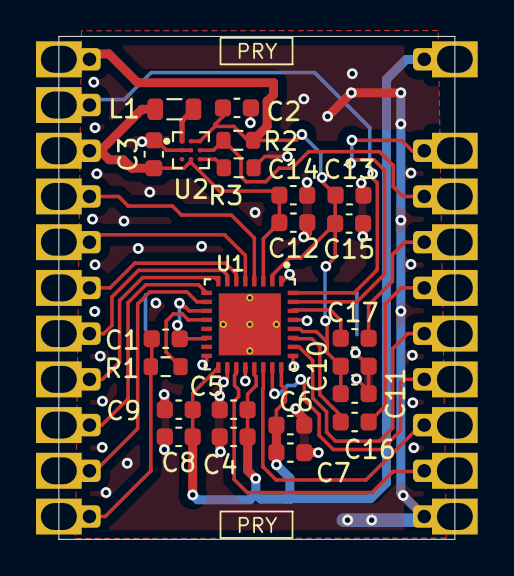
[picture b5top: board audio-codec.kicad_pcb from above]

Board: 2 copper layers, 22.0 x 27.9 mm, 24 parts (1 on the bottom side), 27 nets.
